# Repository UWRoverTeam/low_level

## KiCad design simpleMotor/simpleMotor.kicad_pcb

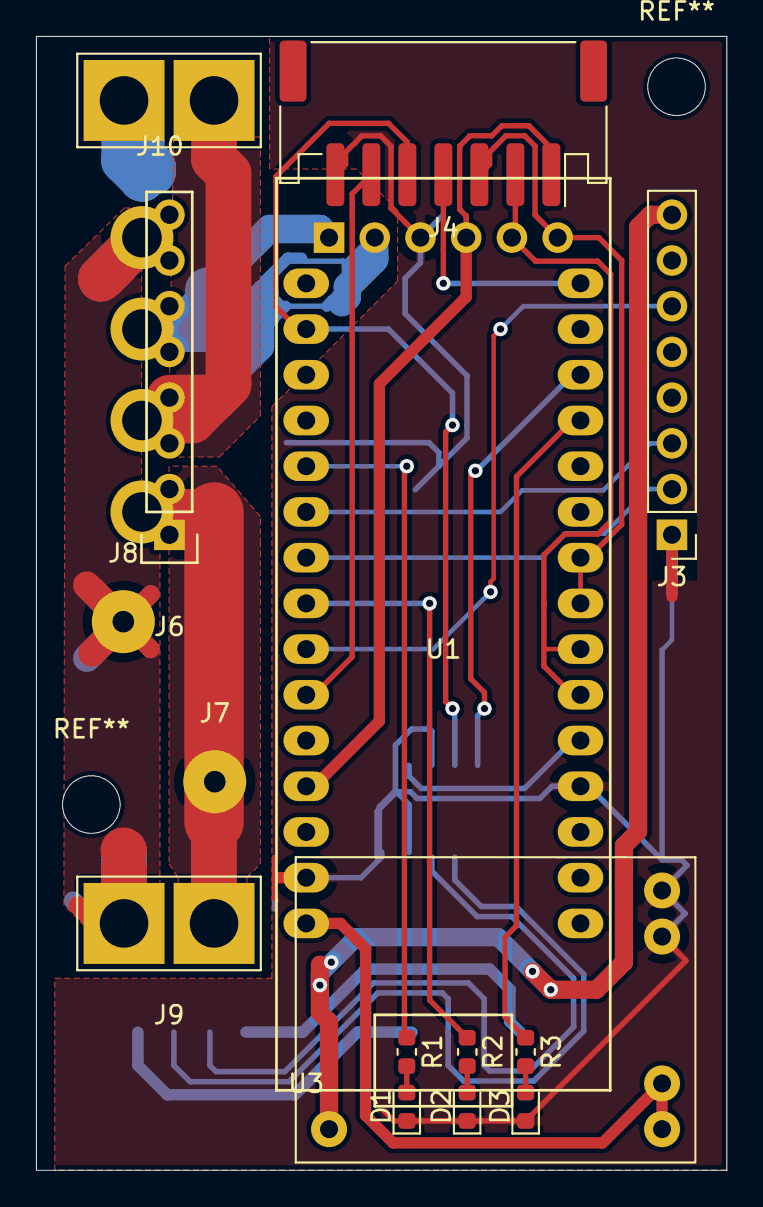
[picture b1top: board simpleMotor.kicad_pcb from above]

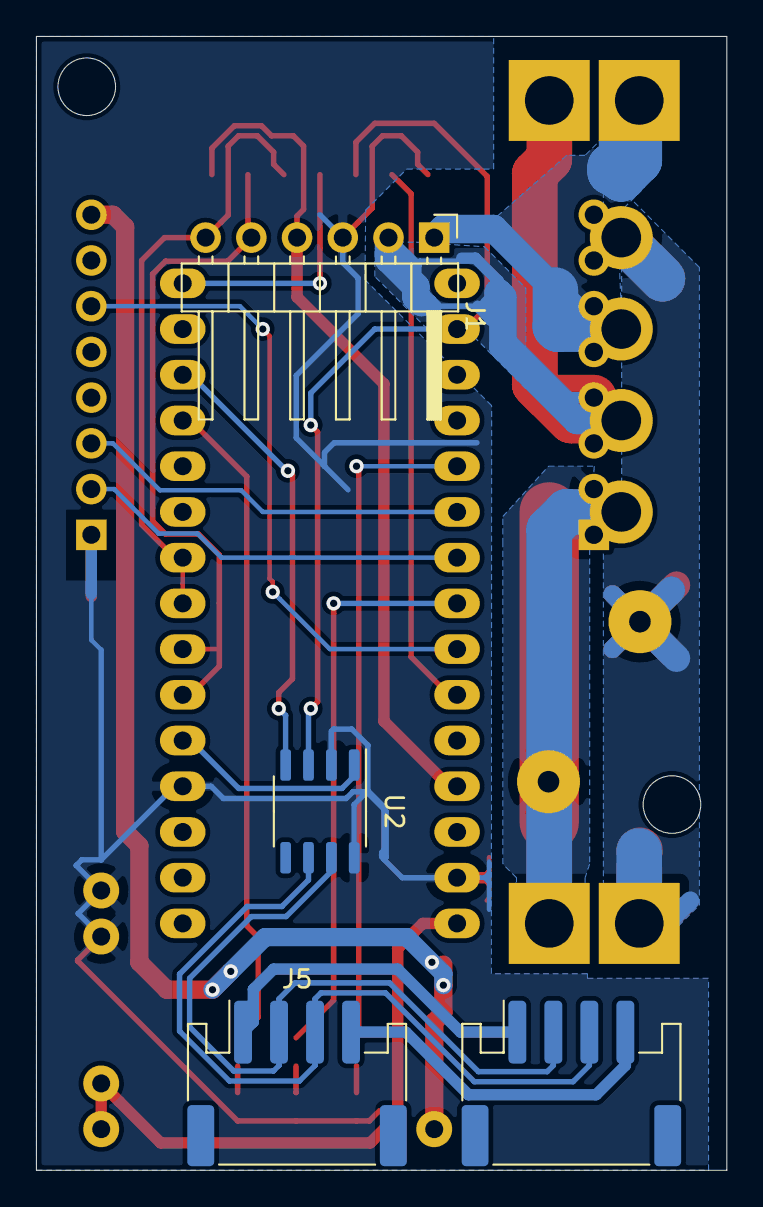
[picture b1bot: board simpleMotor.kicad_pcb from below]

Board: 2 copper layers, 38.4 x 63.0 mm, 19 parts (4 on the bottom side), 27 nets.

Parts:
D1: RED; LED_0603_1608Metric
D2: YELLOW; LED_0603_1608Metric
D3: BLUE; LED_0603_1608Metric
J1: BOTLAND_MOTOR; PinHeader_1x06_P2.54mm_Horizontal
J2: CAN1; JST_PH_S4B-PH-SM4-TB_1x04-1MP_P2.00mm_Horizontal
J3: POLOLU_SIG; Pin_Header_Straight_1x08_Pitch2.54mm
J4: ENCODER; JST_PH_S7B-PH-SM4-TB_1x07-1MP_P2.00mm_Horizontal
J5: CAN2; JST_PH_S4B-PH-SM4-TB_1x04-1MP_P2.00mm_Horizontal
J6: POLOLU_POW; Pin_Header_Pololu_OUT
J7: CAP-; SolderWirePad_1x01_Drill1.2mm
J8: CAP+; SolderWirePad_1x01_Drill1.2mm
J9: BATTERY_IN; XT30_vertical
J10: MOTOR_OUT; XT30_vertical
R1, R2, R3: R; R_0603_1608Metric
U1: NUCLEO-L432KC
U2: SN65HVD231; SO-8_3.9x4.9mm_P1.27mm
U3: step_down_mp1584; mp1584

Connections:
+3V3: J4.5, U1.29, U2.3
+5V: J1.4, J4.1, U1.19
+7.5V: U1.16, U3.3
+24V: J6.4, J8.1, J9.2
ANALOG_ENC: J4.6, U1.21
CAN_RX: U1.13, U2.4
CAN_TX: U1.5, U2.1
CS: J3.6, U1.22
DIR: J3.2, U1.24
ENC_A: J1.5, J4.2, U1.6, U1.7
ENC_B: J1.6, J4.3, U1.8, U1.9
ENC_I: J4.4, U1.15
GND: D1.1, D2.1, D3.1, J1.3, J3.1, J4.7, J6.1, J7.1, J9.1, U1.4, U1.17, U2.2, U2.8, U3.1
LED_BLUE: R3.1, U1.12
LED_R: R1.1, U1.26
LED_YELLOW: R2.1, U1.23
MOTOR_A: J1.2, J6.2, J10.2
MOTOR_B: J1.1, J6.3, J10.1
unnamed: D1.2, R1.2
unnamed: D2.2, R2.2
unnamed: D3.2, R3.2
unnamed: J2.1, J5.1
unnamed: J2.2, J5.2, U2.7
unnamed: J2.3, J5.3, U2.6
unnamed: J2.4, J5.4
PWM: J3.3, U1.25
VM: J3.8, U3.2

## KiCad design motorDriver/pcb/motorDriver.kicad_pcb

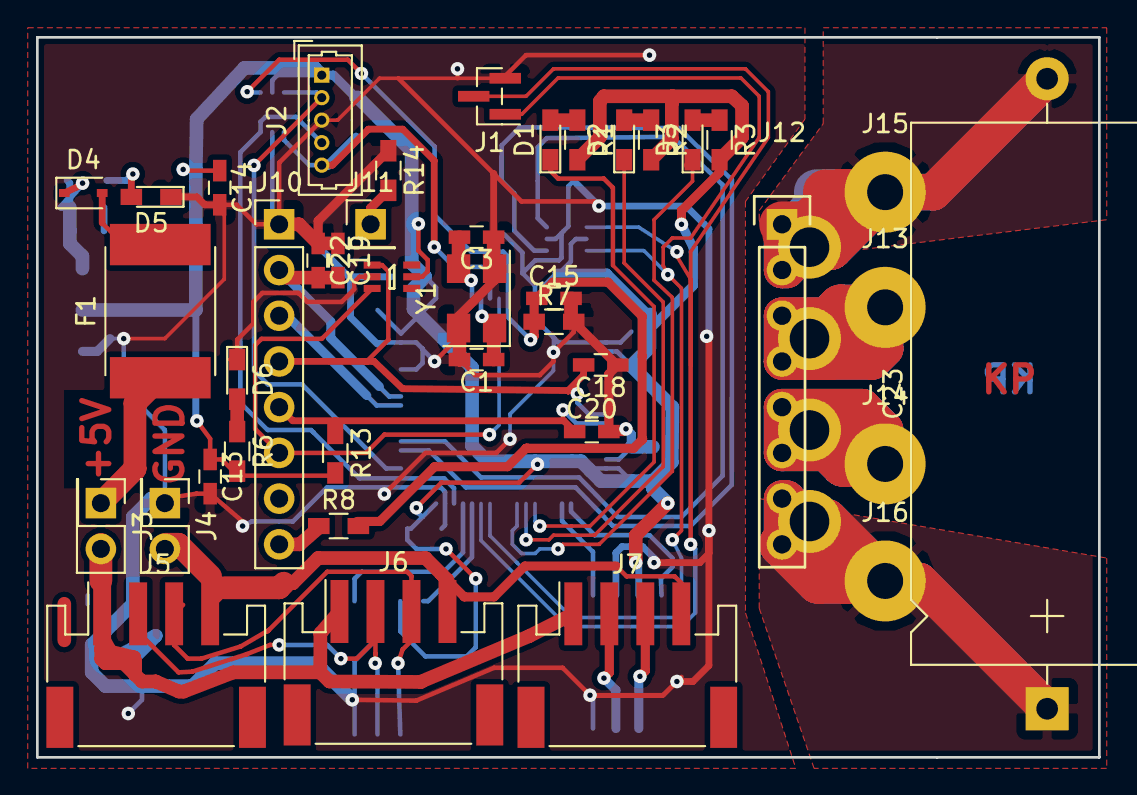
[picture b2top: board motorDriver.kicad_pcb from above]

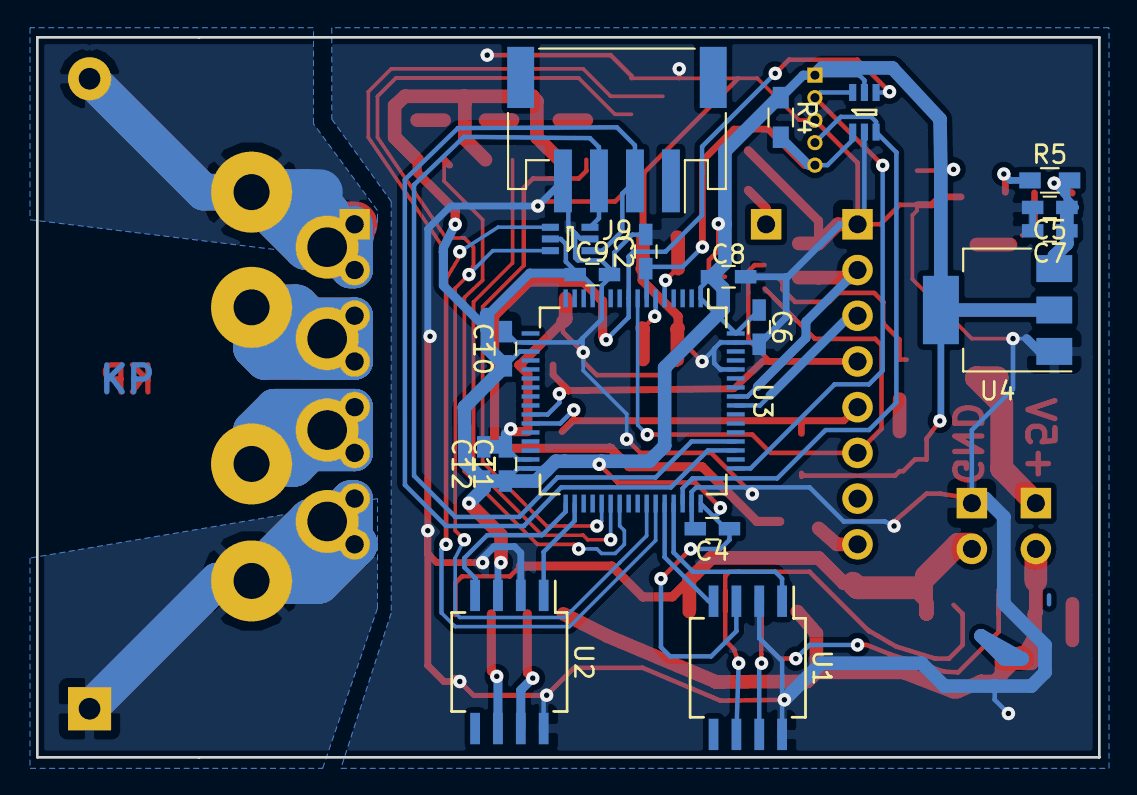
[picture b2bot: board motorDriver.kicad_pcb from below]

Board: 2 copper layers, 59.0 x 40.0 mm, 60 parts (19 on the bottom side), 44 nets.

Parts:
C1, C3: 18p; C_0603_HandSoldering
C2, C4, C6, C7, C8, C9, C10, C11, C14, C15, C18, C20, C22: 100n; C_0603_HandSoldering
C5, C12, C13, C19: 4u7; C_0603_HandSoldering
C23: CP; CP_Axial_L30.0mm_D15.0mm_P35.00mm_Horizontal
D1, D2, D3, D5, D6: LED; LED_0603_HandSoldering
D4: D_Schottky; D_SOD-323
F1: Polyfuse; Fuse_SMD2920
IC1, IC3, IC4: RCLAMP0504F; SC-70-6
J1: DEBUG_SERIAL_CONN; Pin_Header_Straight_1x03_Pitch1.00mm_SMD_Pin1Left
J2: PROG_CONN; Molex_PicoBlade_53047-0510_05x1.25mm_Straight
J3: CAN1_POWER; Pin_Header_Straight_2x01_Pitch2.54mm
J4: CAN1_GND; Pin_Header_Straight_2x01_Pitch2.54mm
J5: CAN1_CONN1; JST_PH_S4B-PH-SM4-TB_04x2.00mm_Angled
J6: CAN1_CONN2; JST_PH_S4B-PH-SM4-TB_04x2.00mm_Angled
J7: CAN2_CONN; JST_PH_S4B-PH-SM4-TB_04x2.00mm_Angled
J9: VESC_CONN; JST_PH_S4B-PH-SM4-TB_04x2.00mm_Angled
J10: POLOLU_CTRL_CONN; Pin_Header_Straight_1x08_Pitch2.54mm
J11: POLOLU_VREF_CONN; Pin_Header_Straight_1x01_Pitch2.54mm
J12: POLOLU_MOTOR_CONN; Pin_Header_Pololu_OUT
J13: MOTOR_A_CONN; SolderWirePad_single_2mmDrill
J14: MOTOR_B_CONN; SolderWirePad_single_2mmDrill
J15: GNDPWR_CONN; SolderWirePad_single_2mmDrill
J16: BATT_CONN; SolderWirePad_single_2mmDrill
R1, R2, R3, R6: 100R; R_0603_HandSoldering
R4, R7, R13: 2k2; R_0603_HandSoldering
R5: 220R; R_0603_HandSoldering
R8: 39k; R_0603_HandSoldering
R14: 47k; R_0603_HandSoldering
U1, U2: SN65HVD231; SO-8_5.3x6.2mm_Pitch1.27mm
U3: STM32F105RBTx; LQFP-64_10x10mm_Pitch0.5mm
U4: LM1117-3.3; SOT-223
Y1: Crystal_GND24; Crystal_SMD_5032-4pin_5.0x3.2mm

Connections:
+5V: D4.2, F1.2
+BATT: C23.1, J12.4, J16.1
ADC1_IN10: IC3.3, J10.6, U3.8
ADC2_IN11: C15.1, IC1.4, R7.1, R8.2, U3.9
CAN1H: J5.2, J6.2, U1.7
CAN1L: J5.3, J6.3, U1.6
CAN1RX: U1.4, U3.44
CAN1TX: U1.1, U3.45
CAN2H: J7.2, U2.7
CAN2L: J7.3, U2.6
CAN2RX: U2.4, U3.33
CAN2TX: U2.1, U3.34
DRV_DIR: C19.2, C22.2, J10.2, U3.57
DRV_PWM: J10.3, U3.56
FAULT: C20.1, J10.5, R13.1, U3.27
GND: C1.2, C2.2, C3.1, C4.2, C5.2, C6.2, C7.2, C8.2, C9.2, C10.2, C11.2, C12.2, C13.2, C14.2, C15.2, C18.1, C19.1, C20.2, C22.1, D5.1, D6.1, IC1.2, IC3.2, IC4.2, J1.3, J2.3, J4.1, J9.4, J10.1, R7.2, R14.1, U1.2, U1.8, U2.2, U2.8, U3.12, U3.18, U3.31, U3.47, U3.60, U3.63, U4.1, Y1.2, Y1.4
GNDPWR: C23.2, J12.1, J15.1
LED1: D1.1, U3.37
LED2: D2.1, U3.38
LED3: D3.1, U3.39
NRST: C2.1, IC1.1, J2.5, R4.2, U3.7
unnamed: C1.1, U3.6, Y1.1
unnamed: C3.2, U3.5, Y1.3
unnamed: C5.1, C7.1, D4.1, R5.2, U4.3
unnamed: D1.2, R1.1
unnamed: D2.2, R2.1
unnamed: D3.2, R3.1
unnamed: D5.2, R5.1
unnamed: D6.2, R6.1
unnamed: F1.1, J3.1
unnamed: J3.2, J5.1, J6.1, J7.1
unnamed: J4.2, J5.4, J6.4, J7.4
unnamed: J11.1, R14.2
unnamed: J12.2, J13.1
unnamed: J12.3, J14.1
SLEEP: C18.2, IC3.1, J10.4, U3.26
SWCLK: IC1.6, J2.2, U3.49
SWDIO: IC1.3, J2.4, U3.46
UART4_RX: IC4.3, J9.3, U3.52
UART4_TX: IC4.1, J9.2, U3.51
USART1_RX: IC4.4, J1.2, U3.43
USART1_TX: IC4.6, J1.1, U3.42
VCC: C4.1, C6.1, C8.1, C9.1, C10.1, C11.1, C12.1, C13.1, C14.1, IC1.5, IC3.5, IC4.5, J2.1, R1.2, R2.2, R3.2, R4.1, R6.2, R13.2, U1.3, U2.3, U3.1, U3.13, U3.19, U3.32, U3.48, U3.64, U4.2, U4.4
VM: J10.8, R8.1

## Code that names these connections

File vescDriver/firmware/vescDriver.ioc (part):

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Mcu.Name=STM32F105R(8-B-C)Tx
Mcu.Package=LQFP64
Mcu.UserName=STM32F105RBTx
PA10.Mode=Asynchronous
PA10.Signal=USART1_RX
PA11.Mode=Master
PA11.Signal=CAN1_RX
PA12.Mode=Master
PA12.Signal=CAN1_TX
PA13.Mode=Serial_Wire
PA13.Signal=SYS_JTMS-SWDIO
PA14.Mode=Serial_Wire
PA14.Signal=SYS_JTCK-SWCLK
PA9.Mode=Asynchronous
PA9.Signal=USART1_TX
PB12.Mode=Slave
PB12.Signal=CAN2_RX
PB13.Mode=Slave
PB13.Signal=CAN2_TX
PC10.Mode=Asynchronous
PC10.Signal=UART4_TX
PC11.Mode=Asynchronous
PC11.Signal=UART4_RX
PC6.GPIOParameters=GPIO_Label
PC6.GPIO_Label=LED1
PC6.Signal=GPIO_Output
PC7.GPIOParameters=GPIO_Label
PC7.GPIO_Label=LED2
PC7.Signal=GPIO_Output
PC8.GPIOParameters=GPIO_Label
PC8.GPIO_Label=LED3
PC8.Signal=GPIO_Output
PD0-OSC_IN.Mode=HSE-External-Oscillator
PD0-OSC_IN.Signal=RCC_OSC_IN
PD1-OSC_OUT.Mode=HSE-External-Oscillator
PD1-OSC_OUT.Signal=RCC_OSC_OUT
RCC.SYSCLKFreq_VALUE=72000000
RCC.SYSCLKSource=RCC_SYSCLKSOURCE_PLLCLK
board=vescDriver

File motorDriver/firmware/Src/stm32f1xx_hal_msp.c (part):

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    __HAL_RCC_ADC1_CLK_ENABLE();
  
    /**ADC1 GPIO Configuration    
    PC0     ------> ADC1_IN10 
    */
    GPIO_InitStruct.Pin = GPIO_PIN_0;
    GPIO_InitStruct.Mode = GPIO_MODE_ANALOG;
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    __HAL_RCC_ADC2_CLK_ENABLE();
  
    /**ADC2 GPIO Configuration    
    PC1     ------> ADC2_IN11 
    */
    GPIO_InitStruct.Pin = GPIO_PIN_1;
    GPIO_InitStruct.Mode = GPIO_MODE_ANALOG;
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    __HAL_RCC_ADC1_CLK_DISABLE();
  
    /**ADC1 GPIO Configuration    
    PC0     ------> ADC1_IN10 
    */
    HAL_GPIO_DeInit(GPIOC, GPIO_PIN_0);

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    __HAL_RCC_ADC2_CLK_DISABLE();
  
    /**ADC2 GPIO Configuration    
    PC1     ------> ADC2_IN11 
    */
    HAL_GPIO_DeInit(GPIOC, GPIO_PIN_1);

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    __HAL_RCC_UART4_CLK_ENABLE();
  
    /**UART4 GPIO Configuration    
    PC10     ------> UART4_TX
    PC11     ------> UART4_RX 
    */
    GPIO_InitStruct.Pin = GPIO_PIN_10;
    GPIO_InitStruct.Mode = GPIO_MODE_AF_PP;
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    __HAL_RCC_USART1_CLK_ENABLE();
  
    /**USART1 GPIO Configuration    
    PA9     ------> USART1_TX
    PA10     ------> USART1_RX 
    */
    GPIO_InitStruct.Pin = GPIO_PIN_9;
    GPIO_InitStruct.Mode = GPIO_MODE_AF_PP;
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    __HAL_RCC_UART4_CLK_DISABLE();
  
    /**UART4 GPIO Configuration    
    PC10     ------> UART4_TX
    PC11     ------> UART4_RX 
    */
    HAL_GPIO_DeInit(GPIOC, GPIO_PIN_10|GPIO_PIN_11);

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    __HAL_RCC_USART1_CLK_DISABLE();
  
    /**USART1 GPIO Configuration    
    PA9     ------> USART1_TX
    PA10     ------> USART1_RX 
    */
    HAL_GPIO_DeInit(GPIOA, GPIO_PIN_9|GPIO_PIN_10);

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
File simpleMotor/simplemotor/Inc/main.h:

/* USER CODE BEGIN Header */
/**
  ******************************************************************************
  * @file           : main.h
  * @brief          : Header for main.c file.
  *                   This file contains the common defines of the application.
  ******************************************************************************
  * @attention
  *
  * <h2><center>&copy; Copyright (c) 2020 STMicroelectronics.
  * All rights reserved.</center></h2>
  *
  * This software component is licensed by ST under BSD 3-Clause license,
  * the "License"; You may not use this file except in compliance with the
  * License. You may obtain a copy of the License at:
  *                        opensource.org/licenses/BSD-3-Clause
  *
  ******************************************************************************
  */
/* USER CODE END Header */

/* Define to prevent recursive inclusion -------------------------------------*/
#ifndef __MAIN_H
#define __MAIN_H

#ifdef __cplusplus
extern "C" {
#endif

/* Includes ------------------------------------------------------------------*/
#include "stm32l4xx_hal.h"

/* Private includes ----------------------------------------------------------*/
/* USER CODE BEGIN Includes */

/* USER CODE END Includes */

/* Exported types ------------------------------------------------------------*/
/* USER CODE BEGIN ET */

/* USER CODE END ET */

/* Exported constants --------------------------------------------------------*/
/* USER CODE BEGIN EC */

/* USER CODE END EC */

/* Exported macro ------------------------------------------------------------*/
/* USER CODE BEGIN EM */

/* USER CODE END EM */

void HAL_TIM_MspPostInit(TIM_HandleTypeDef *htim);

/* Exported functions prototypes ---------------------------------------------*/
void Error_Handler(void);

/* USER CODE BEGIN EFP */

/* USER CODE END EFP */

/* Private defines -----------------------------------------------------------*/
#define MCO_Pin GPIO_PIN_0
#define MCO_GPIO_Port GPIOA
#define LED_G_Pin GPIO_PIN_1
#define LED_G_GPIO_Port GPIOA
#define VCP_TX_Pin GPIO_PIN_2
#define VCP_TX_GPIO_Port GPIOA
#define PWM_Pin GPIO_PIN_3
#define PWM_GPIO_Port GPIOA
#define DIR_Pin GPIO_PIN_4
#define DIR_GPIO_Port GPIOA
#define LED_Y_Pin GPIO_PIN_5
#define LED_Y_GPIO_Port GPIOA
#define CS_Pin GPIO_PIN_6
#define CS_GPIO_Port GPIOA
#define ENC_ANALOG_Pin GPIO_PIN_7
#define ENC_ANALOG_GPIO_Port GPIOA
#define ENC_A_Pin GPIO_PIN_0
#define ENC_A_GPIO_Port GPIOB
#define ENC_B_Pin GPIO_PIN_1
#define ENC_B_GPIO_Port GPIOB
#define LED_B_Pin GPIO_PIN_8
#define LED_B_GPIO_Port GPIOA
#define CAN_RX_Pin GPIO_PIN_11
#define CAN_RX_GPIO_Port GPIOA
#define CAN_TX_Pin GPIO_PIN_12
#define CAN_TX_GPIO_Port GPIOA
#define SWDIO_Pin GPIO_PIN_13
#define SWDIO_GPIO_Port GPIOA
#define SWCLK_Pin GPIO_PIN_14
#define SWCLK_GPIO_Port GPIOA
#define VCP_RX_Pin GPIO_PIN_15
#define VCP_RX_GPIO_Port GPIOA
#define LD3_Pin GPIO_PIN_3
#define LD3_GPIO_Port GPIOB
#define ENC_I_Pin GPIO_PIN_4
#define ENC_I_GPIO_Port GPIOB
/* USER CODE BEGIN Private defines */

/* USER CODE END Private defines */

#ifdef __cplusplus
}
#endif

#endif /* __MAIN_H */

/************************ (C) COPYRIGHT STMicroelectronics *****END OF FILE****/

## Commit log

2019-07-04 init commit
2019-07-09 shared folder added
2021-12-13 AHRS - comment added
2021-12-13 PID parameters can be set remotely for VESCdriver and motorDriver
2021-12-13 added simpleMotor driver

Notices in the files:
motorDriver/firmware/Src/stm32f1xx_hal_msp.c:
COPYRIGHT(c) 2018 STMicroelectronics
